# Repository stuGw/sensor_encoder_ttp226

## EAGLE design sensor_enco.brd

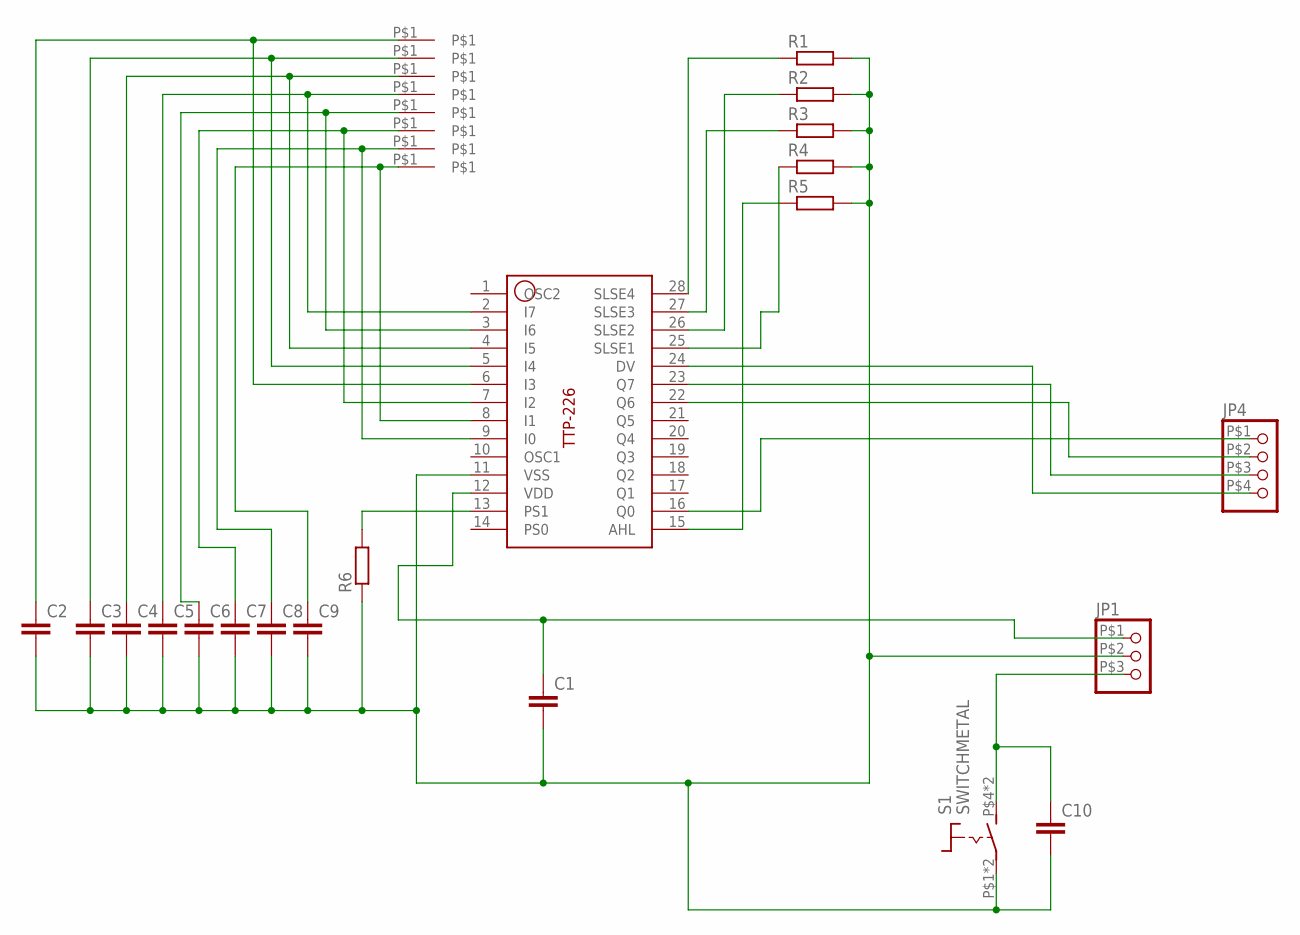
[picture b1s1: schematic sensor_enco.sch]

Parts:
C1, C2, C3, C4, C5, C6, C7, C8, C9, C10: C-EUC0402; C0402
JP1: PINHD-1X32MM; 1X03_2MM
JP4: PINHD-1X42MM; 1X04_2MM
R1, R2, R3, R4, R5, R6: R-EU_R0402; R0402
S1: SWITCHMETAL; SWMET
U$1, U$2, U$10, U$11, U$12, U$13, U$14, U$15: SENSOR_PADSENSORPAD3; SENSOR_PAD3
U$9: TTP-226LIBTOUCH-TTP226; TSSOP28

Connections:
unnamed: C3.1, U$2.P$1, U$9.5 (I4)
unnamed: C2.1, U$1.P$1, U$9.6 (I3)
unnamed: R3.1, U$9.27 (SLSE3)
unnamed: C9.1, U$9.8 (I1), U$15.P$1
unnamed: C7.1, U$9.7 (I2), U$13.P$1
unnamed: C4.1, U$9.4 (I5), U$10.P$1
unnamed: C5.1, U$9.2 (I7), U$11.P$1
unnamed: C8.1, U$9.9 (I0), U$14.P$1
unnamed: JP4.P$3 (3), U$9.23 (Q7)
unnamed: JP4.P$4 (4), U$9.24 (DV)
unnamed: JP4.P$2 (2), U$9.22 (Q6)
unnamed: R1.1, U$9.28 (SLSE4)
unnamed: C1.2, C2.2, C3.2, C4.2, C5.2, C6.2, C7.2, C8.2, C9.2, C10.2, JP1.P$2 (2), R1.2, R2.2, R3.2, R4.2, R5.2, R6.1, S1.P$1, S1.P$1@1, U$9.11 (VSS)
unnamed: C1.1, JP1.P$1 (1), U$9.12 (VDD)
unnamed: R2.1, U$9.26 (SLSE2)
unnamed: R6.2, U$9.13 (PS1)
unnamed: JP4.P$1 (1), U$9.16 (Q0)
unnamed: C10.1, JP1.P$3 (3), S1.P$4 (S), S1.P$4@1 (S)
unnamed: R5.1, U$9.15 (AHL)
unnamed: R4.1, U$9.25 (SLSE1)
unnamed: C6.1, U$9.3 (I6), U$12.P$1

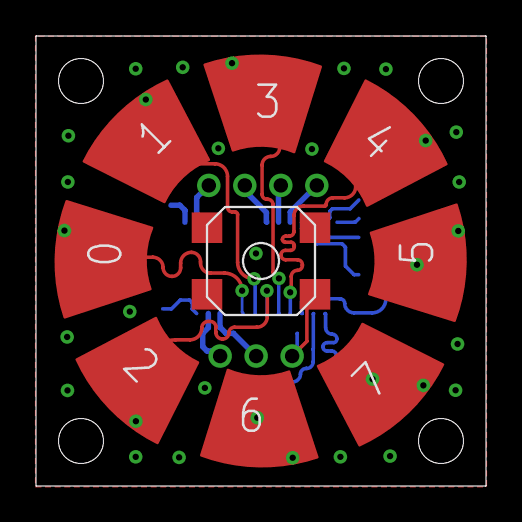
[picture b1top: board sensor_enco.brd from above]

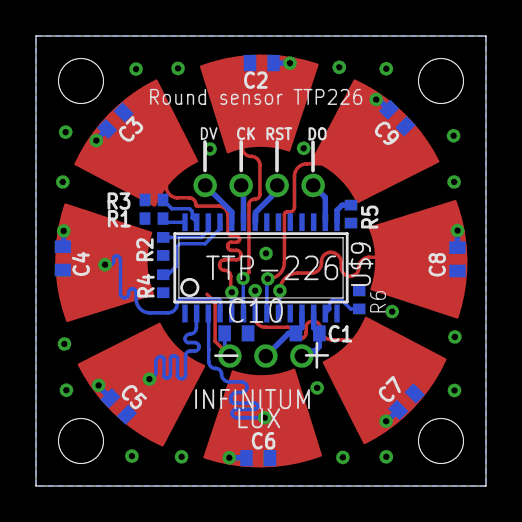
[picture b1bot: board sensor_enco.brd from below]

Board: 2 copper layers, 25.0 x 25.0 mm, 28 parts (17 on the bottom side), 21 nets.

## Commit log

2023-03-24 first
2023-03-29 some changes
2023-04-14 release
